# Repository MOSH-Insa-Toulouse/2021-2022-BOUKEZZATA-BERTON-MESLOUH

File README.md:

# 2021-2022-BOUKEZZATA-BERTON-MESLOUH

<div id="top"></div>
<!--
*** Thanks for checking out the Best-README-Template. If you have a suggestion
*** that would make this better, please fork the repo and create a pull request
*** or simply open an issue with the tag "enhancement".
*** Don't forget to give the project a star!
*** Thanks again! Now go create something AMAZING! :D
-->

<!-- PROJECT SHIELDS -->
<!--
*** I'm using markdown "reference style" links for readability.
*** Reference links are enclosed in brackets [ ] instead of parentheses ( ).
*** See the bottom of this document for the declaration of the reference variables
*** for contributors-url, forks-url, etc. This is an optional, concise syntax you may use.
*** https://www.markdownguide.org/basic-syntax/#reference-style-links
-->
<!-- PROJECT LOGO -->
<br />
<div align="center">
  
  <h3 align="center">Smart Device</h3>
</div>

<!-- TABLE OF CONTENTS -->
<details>
  <summary>Table of Contents</summary>
  <ol>
    <li>
      <a href="#about-the-project">About The Project</a>
    </li>
    <li>
      <a href="#lora">Lora</a>
    </li>
    <li>
      <a href="#lorawan">LoRAWAN</a>
    </li>
    <li><a href="#kicad">KiCAD</a></li>
    <li><a href="#node-red">Node-Red</a></li>
    <li><a href="#datasheet">DATASHEET</a></li>
  </ol>
</details>

<!-- ABOUT THE PROJECT -->
## About The Project
After manufacturing the gas sensor, we would like to design a system from an ESP32 microcontroller to retrieve the data collected from the sensor and communicate the detection of a specefic gas towards a server with a LoRA module

<p align="right">(<a href="#top">back to top</a>)</p>

<!-- GETTING STARTED -->
## LoRA

We used the <a href="https://github.com/jpmeijers/RN2483-Arduino-Library.git"> RN2483@jpmeijers </a> library to connect the Lora module to the TTN server "The Things Network".

We've connected the 3 pins of the LoRA module to the ESP32
<br/>
```cpp
#define RST 21 //Pin de reset du module LORA
#define RX 18  //Pin RX du module LORA
#define TX 19  //Pin TX du module LORA
```
And We used the serial port 2 (baud 57600) of the ESP32 to communicate with the RN2483
```cpp
rn2xx3 lora(Serial2);
```
To use the simple radio communication. you have to send with the serial monitor connected to your PC this commande (`radio tx "hexa_msg"`)

<br/>
To receive radio communication, you only have to listene on the serail port 2
All the RN2483 command lines end with "\r\n"

```cpp
void initialize_radio()
{
  pinMode(RESET, OUTPUT);
  digitalWrite(RESET, LOW);
  delay(100);
  digitalWrite(RESET, HIGH); //reset the RN2483

  delay(100); //wait for the RN2xx3's startup message
  Serial2.flush();
}

void setup()
{
  Serial.begin(9600);
  Serial2.begin(57600, SERIAL_8N1, RXD2, TXD2);
  initialize_radio();
  Serial.println(Serial2.readStringUntil('\n'));
  Serial2.print("radio set pwr 14\r\n");
  Serial.println(Serial2.readStringUntil('\n'));
  Serial2.print("mac pause\r\n");
  Serial.println(Serial2.readStringUntil('\n'));
}

void loop()
{
  if(Serial2.available()) {
    Serial.println(Serial2.readStringUntil('\n'));
  }
  if (Serial.available())
  { 
    String Command = Serial.readStringUntil('\n');
    Serial.println(Command);
    Serial2.print(Command + "\r\n");
  }
}
```

## LoRAWAN

To connect to the TTN server, you have to copy past the UEI key of the RN2483 with this command (` sys get hwuei `) to this line

```ccp
String AppEUI = "44E53245F1200CDEEC2525661C76BA38"; //AppEUI du reseau sur TTN
```
Then initialze the LoRAWAN module

```cpp
void initialize_LoRAWAN();
```

## KiCAD

* The sensors are connected to an SPDT switch to commute between the two of them
* The resistor R6 is required to obtain the value of R_Alu.

* The operational amplifier (LTC1050) is used to filter and amplify the current passing through the sensors' resistance
* The amplifier must have a low offset votage
* To read the value of the gas sensor you ave to use this command 
```cpp
uint32_t read_aime_sensor () //Recuperation de la donnée du capteur AIME
{
  int sensor_aime_Value = analogRead(ADC_SENS);
  sensor_aime_volt=(float)sensor_aime_Value/4096*V3_3;
  float R_capteur=(1+R3/R2)*R1*V3_3/sensor_aime_volt-R1-R5; //formule justifiée en TD
  return R_capteur;
}
```

* The gas sensor works at least at a temperature of 200°C, so we control the R_poly heater with a PWM from the ESP32, and correct the system error with a PID.
* the resistor R4 is to define the current of the transistor surce (`Is = beta * Ib`)
* You have to define (`a`) and (`b`) of the temparture sensor
```cpp
int a; //
int b; // R_aluminium = a * T(Kelvin) + b 

float temperature () // mesure de la temperature du capteur en fonction de R aluminium
{
  float T = a*(read_r_alu()) + b;
  T = T - 273; //conversion en Celcius
  return T;
}

```
---
```cpp
int manage_PID(int consigne, int kp, int ki, int kd) //Correcteur PID pour maintenir la temprature a 200 degrés celcius
{
  int t_2 = micros();
  float delta_t = ((float) (t_2 - t_1))/1E6
  t_1 = t_2;

  e_t = consigne - temperature();
  e_integral = e_integral + e_t * delta_t; 
  float e_D = (e_t - e_t_1) / (delta_t);
  uint8_t C = kp*e_t + ki*e_integral + kd*e_D;

  t_2 = t_1;
  e_t_1 = e_t;

  C = fabs(C);

  if(C > 255) C = 255; //Pour borner la correction entre 0 et 255
 
  return C; //Duty cycle de la PWM de commande
}

void Cmd_PWM_Poly(int duty_cycle) //Commande de la resistance de chauffe en PWM
{
  ledcWrite(ledChannel,duty_cyle);
}
```

* The comparator (LT071) is used to release an interrupt on the ESP32 when the sensor detect a certain gas
* We have defined a refrence voltage on the V+ whith a volatage divider R7 and R8
* If the sensor detect a gas, the sensor voltage ADC dropdown and the output LT071 will be 1

we designed the PCB.

## Node-Red
For the last part, we needed an application to setup the system and a dashboard to display the sensor values. For this, we used Node-red to connect the gas sensor with the TTN server via LORAWAN communication.

The dashboard of the system

## DATASHEET

you can find the datasheet <a href="/Assets/Datasheet_AIME_git.pdf" target="_blank"> HERE </a>

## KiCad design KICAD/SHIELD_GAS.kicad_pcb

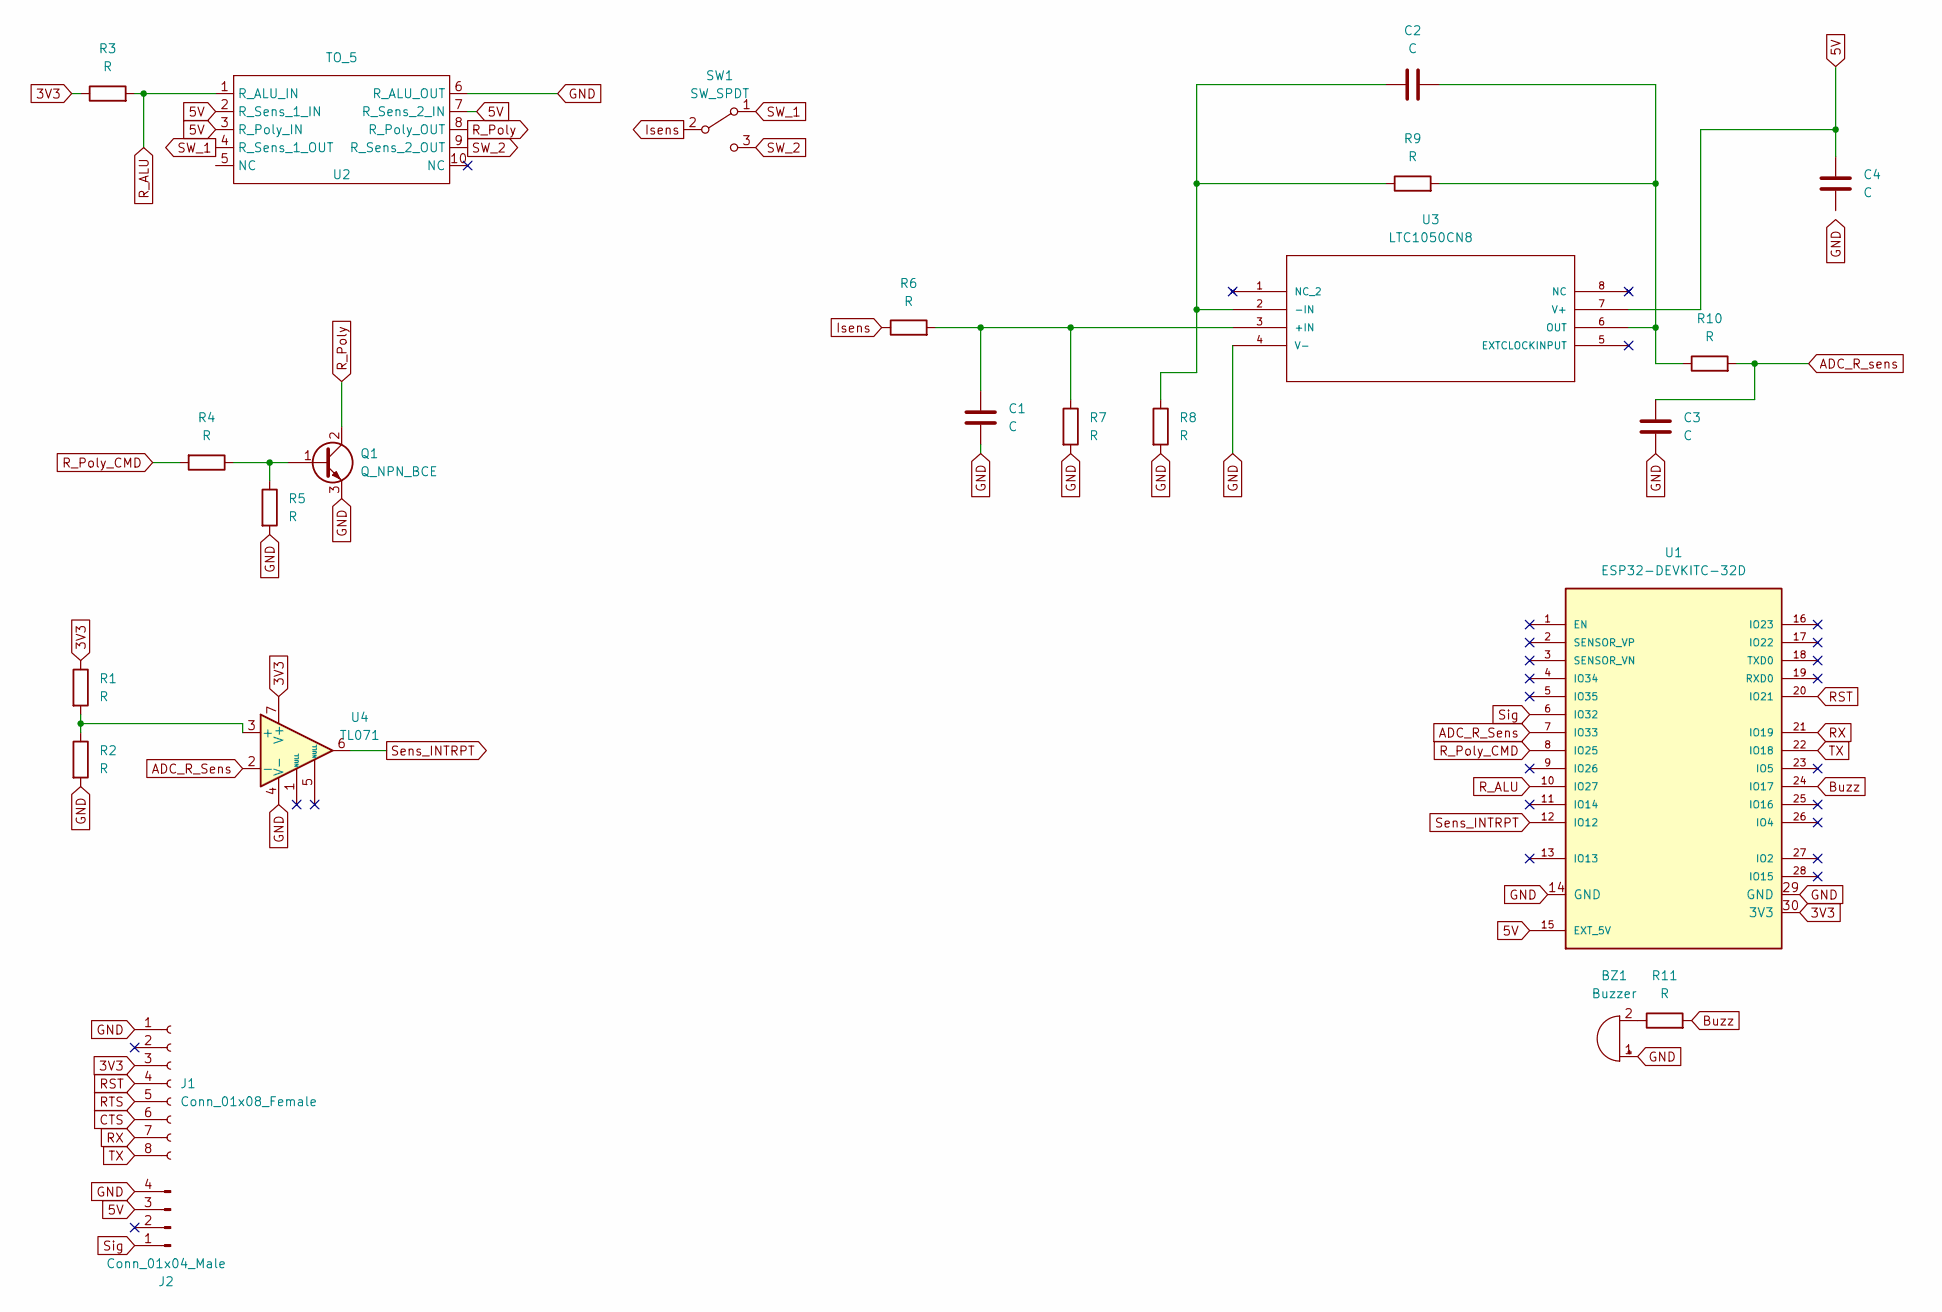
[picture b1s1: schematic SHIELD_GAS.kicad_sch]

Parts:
BZ1: Buzzer; Buzzer_12x9.5RM7.6
C1, C2, C3, C4: C; C_Axial_L3.8mm_D2.6mm_P7.50mm_Horizontal
J1: Conn_01x08_Female; PinSocket_1x08_P2.54mm_Vertical
J2: Conn_01x04_Male; JST_PH_B4B-PH-K_1x04_P2.00mm_Vertical
Q1: Q_NPN_BCE; TO-92
R1, R2, R3, R4, R5, R6, R7, R8, R9, R10, R11: R; R_Axial_DIN0411_L9.9mm_D3.6mm_P12.70mm_Horizontal
SW1: SW_SPDT; SW_CuK_OS102011MA1QN1_SPDT_Angled
U1: ESP32-DEVKITC-32D; MODULE_ESP32-DEVKITC-32D; PARTREV 4
U2: TO_5; TO-5
U3: LTC1050CN8; DIP-8_W7.62mm_LongPads; MANUFACTURER_PART_NUMBER ltc1050cn8
U4: TL071; DIP-8_W7.62mm_LongPads

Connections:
3V3: J1.3, R1.1, R3.1, U1.30 (3V3), U4.7 (V+)
5V: C4.1, J2.3, U1.15 (EXT_5V), U2.2 (R_Sens_1_IN), U2.3 (R_Poly_IN), U2.7 (R_Sens_2_IN), U3.7 (V+)
ADC_R_Sens: U1.7 (IO33), U4.2 (-)
ADC_R_sens: C3.1, R10.2
Buzz: R11.2, U1.24 (IO17)
CTS: J1.6
GND: BZ1.1 (-), C1.2, C3.2, C4.2, J1.1, J2.4, Q1.3 (E), R2.2, R5.2, R7.2, R8.2, U1.14 (GND), U1.29 (GND), U2.6 (R_ALU_OUT), U3.4 (V-), U4.4 (V-)
Isens: R6.1, SW1.2 (B)
unnamed: BZ1.2 (+), R11.1
unnamed: C1.1, R6.2, R7.1, U3.3 (+IN)
unnamed: C2.1, R8.1, R9.1, U3.2 (-IN)
unnamed: C2.2, R9.2, R10.1, U3.6 (OUT)
unnamed: Q1.1 (B), R4.1, R5.1
unnamed: R1.2, R2.1, U4.3 (+)
RST: J1.4, U1.20 (IO21)
RTS: J1.5
RX: J1.7, U1.21 (IO19)
R_ALU: R3.2, U1.10 (IO27), U2.1 (R_ALU_IN)
R_Poly: Q1.2 (C), U2.8 (R_Poly_OUT)
R_Poly_CMD: R4.2, U1.8 (IO25)
SW_1: SW1.1 (A), U2.4 (R_Sens_1_OUT)
SW_2: SW1.3 (C), U2.9 (R_Sens_2_OUT)
Sens_INTRPT: U1.12 (IO12), U4.6
Sig: J2.1, U1.6 (IO32)
TX: J1.8, U1.22 (IO18)

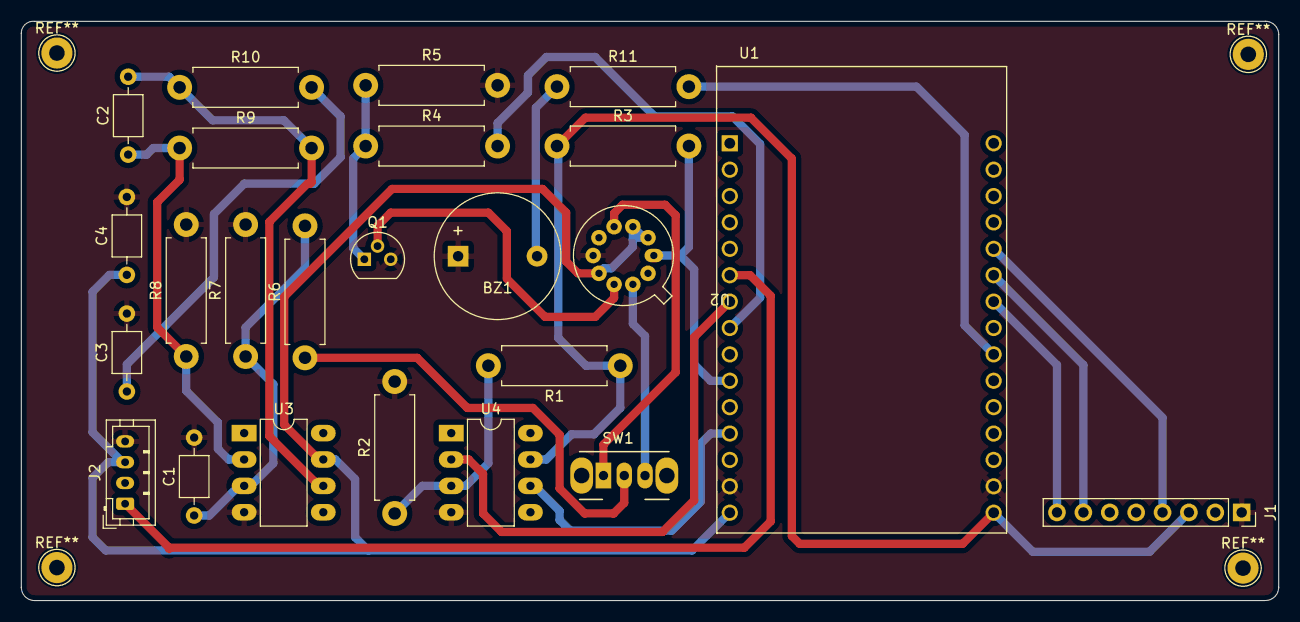
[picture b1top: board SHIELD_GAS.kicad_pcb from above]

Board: 2 copper layers, 121.0 x 55.8 mm, 24 parts (0 on the bottom side), 23 nets.

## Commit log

2021-12-06 MOSH PROJECT CPP
2021-12-06 Create MOSH PROJECT CPP CODE
2021-12-06 Create hello
2021-12-29 Kicad
2022-01-01 pics

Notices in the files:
parts and their libraries:
COPYRIGHT: Copyright C 2016 Accelerated Designs. All rights reserved
